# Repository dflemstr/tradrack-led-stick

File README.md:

# Tradrack LED stick

This is a mod for Annex Engineering's [TradRack][1] that enables the addition
of LED light indicators for each filament gate/lane.

Since the lanes are spaced at a 17mm pitch, there are no regular LED strips
that would fit a Tradrack with a large number of lanes (I myself use ~35 lanes),
hence the need for this project.

This project is not an official Annex Engineering project and bears no
affiliation with the Annex Engineering organization.  The project is licensed
under the terms of GPL-3.

There are various software options available for controlling these LEDs,
for example by using the [Happy Hare][2] software to control the Tradrack.

For now there's only a PCB design in this repo.  I might eventually add
some 3D-printable parts that aid in mounting the LED boards.

## Fabrication

You can easily get the PCBs fabricated at various PCB shops.  I provide
easy-to-use files for fabrication using [JLCPCB][3] in the `pcb/fabrication-outputs` folder.
Simply upload the files to JLCPCB's assembly service and everything
should mostly just work.

## Mounting

The PCBs are designed with a 17mm pitch which should match the Tradrack lane
spacing.  You can join the PCB with a short piece of wire, a solder bridge,
or a JST-XH straight-through connector.  The PCBs are designed with a 1mm
gap between them to allow for some adjustment when aligning multiple PCBs,
in case the lanes or the PCBs themselves have some imperfections.

**Note**: The LED stick is designed to be adaptable to the [Voron Daylight Disco][4]
pinout.  However, due to space constraints (because the stick needs to maintain the
17mm spacing), there isn't enough room on the board to solder a "normal" or "flipped"
JST-XH connector.  Instead, take a vertical JST-XH connector, and bend the legs 90 degrees
towards the side of the connector housing that has 2 slots.  Then, solder the connector from
above onto the LED stick, letting it hang out over the side of the board.  If done
correctly, the board will be pin-compatible with the Voron Daylight Disco board.

Here are some photos of a finished soldering job for reference:

The PCBs are also designed to be easy to cut at an arbitrary point without
causing a short.  Cutting the PCB between any two LEDs should be easily done
with a hack saw/rotary cutter/...  Just make sure to use appropriate protective
equipment and maybe have a spare stick in case something goes wrong.

### LED profile

I am using a LED profile to mount the LED PCBs into.  The size I'm using is
fairly common in hardware stores, with a 17mm outside width, 6.5mm thick
(without the diffuser), and has a 12mm inner channel.

To mount the PCBs this way, I used thermal double sided tape (to aid with
heat dissipation -- although it shouldn't be strictly needed) and then
the 3D printed mounting bracket in [`led-profile-holder`](./led-profile-holder).

This assembly can then be mounted at the front of the Trad Rack, in between the 2020
and the cable chain.

It is also necessary to use low-profile M5 bolts for any parts that are mounted to
the front of the Trad Rack extrusion (the `idler_pulley_mount` and `motor_mount_lower`)
if the filament lane modules are mounted in such a way that the corresponding LEDs need
to be in front of these parts. I use [OpenBuilds low profile M5 screws][5], 8mm long.

For the cable chain anchor, a lowered version is needed.  I've included one in the
[`led-profile-holder`](./led-profile-holder) directory.

There won't be any room for other front-mounted parts on the 2020 that stick out more
than 7mm.  For example, you can use [this mount][6] for an ERCF Easy BRD to mount the
board from the bottom of the extrusion instead of the side.

[1]: https://github.com/Annex-Engineering/TradRack
[2]: https://github.com/moggieuk/Happy-Hare/blob/main/doc/leds.md
[3]: https://jlcpcb.com/
[4]: https://github.com/VoronDesign/Voron-Hardware/tree/master/Daylight/Disco_on_a_stick
[5]: https://openbuildspartstore.com/low-profile-screws-m5-10-pack-/
[6]: https://www.printables.com/model/481199-ercf-easybrdcan-brd-mount-for-tr

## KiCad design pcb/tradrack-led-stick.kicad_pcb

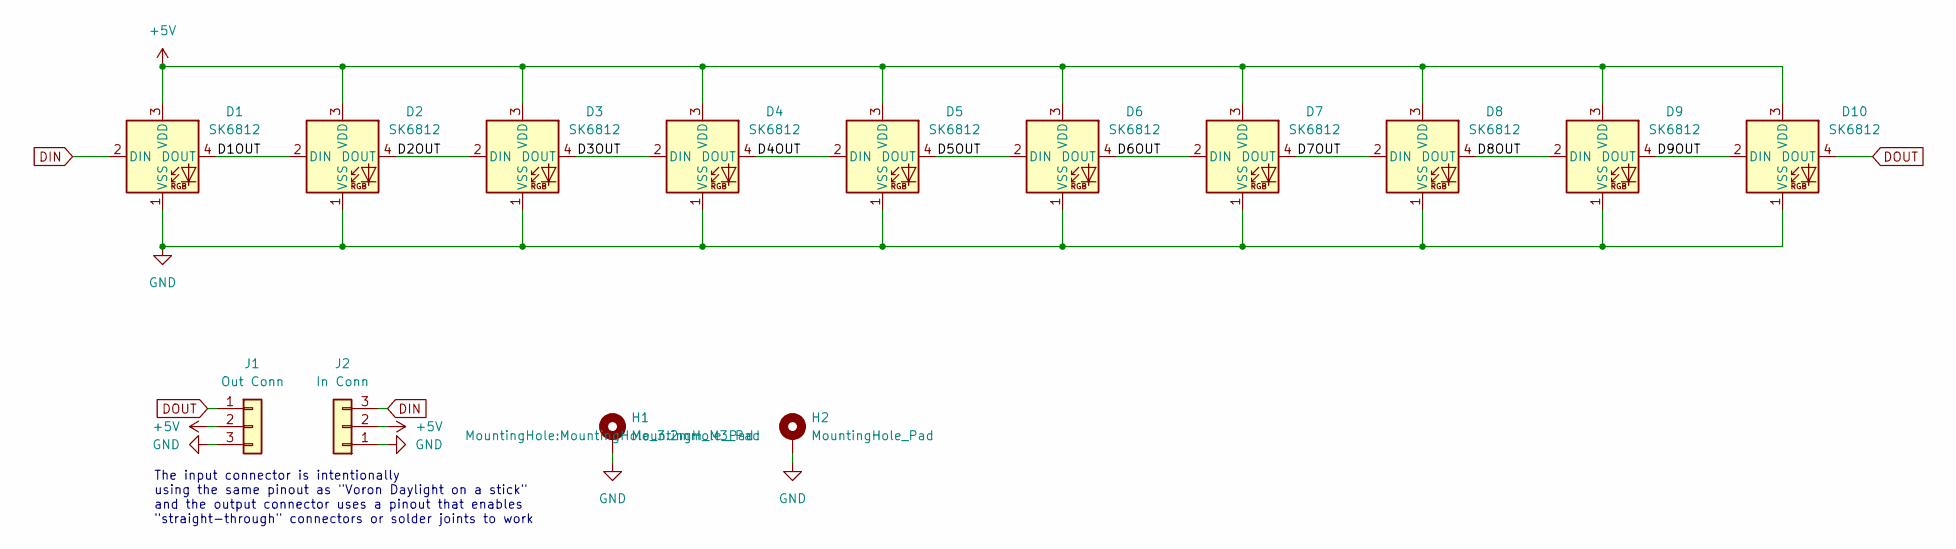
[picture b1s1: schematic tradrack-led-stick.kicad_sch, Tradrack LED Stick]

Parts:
D1, D2, D3, D4, D5, D6, D7, D8, D9, D10: SK6812; LED_SK6812_PLCC4_5.0x5.0mm_P3.2mm; MPN SKC6812RGBW-NW-B; LCSC C5380880
H1, H2: MountingHole_Pad; MountingHole_3.2mm_M3_Pad
J1: Out Conn; JST_XH_B3B-XH-A_1x03_P2.50mm_Vertical
J2: In Conn; JST_XH_B3B-XH-A_1x03_P2.50mm_Vertical

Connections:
+5V: D1.3 (VDD), D2.3 (VDD), D3.3 (VDD), D4.3 (VDD), D5.3 (VDD), D6.3 (VDD), D7.3 (VDD), D8.3 (VDD), D9.3 (VDD), D10.3 (VDD), J1.2, J2.2
/D1OUT: D1.4 (DOUT), D2.2 (DIN)
/D2OUT: D2.4 (DOUT), D3.2 (DIN)
/D3OUT: D3.4 (DOUT), D4.2 (DIN)
/D4OUT: D4.4 (DOUT), D5.2 (DIN)
/D5OUT: D5.4 (DOUT), D6.2 (DIN)
/D6OUT: D6.4 (DOUT), D7.2 (DIN)
/D7OUT: D7.4 (DOUT), D8.2 (DIN)
/D8OUT: D8.4 (DOUT), D9.2 (DIN)
/D9OUT: D9.4 (DOUT), D10.2 (DIN)
DIN: D1.2 (DIN), J2.3
DOUT: D10.4 (DOUT), J1.1
GND: D1.1 (VSS), D2.1 (VSS), D3.1 (VSS), D4.1 (VSS), D5.1 (VSS), D6.1 (VSS), D7.1 (VSS), D8.1 (VSS), D9.1 (VSS), D10.1 (VSS), H1.1, H2.1, J1.3, J2.1

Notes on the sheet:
The input connector is intentionally using the same pinout as "Voron Daylight on a stick" and the output connector uses a pinout that enables "straight-through" connectors or solder joints to work

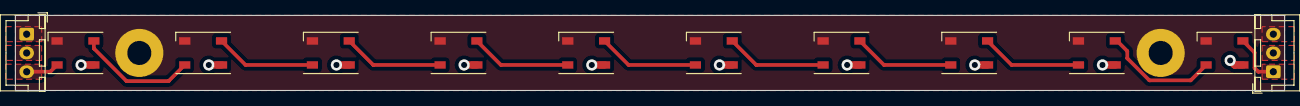
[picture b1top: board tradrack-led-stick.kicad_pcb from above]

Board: 2 copper layers, 169.0 x 10.0 mm, 14 parts (0 on the bottom side), 13 nets.

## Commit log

2024-01-07 Add ignore file
2024-01-07 Publish v1 of the PCB
2024-01-07 Add rendered image
2024-01-17 Remove stray kicad file
2024-01-17 Add 3D printed LED profile holder
2024-01-19 Switch to a straight LED profile instead
